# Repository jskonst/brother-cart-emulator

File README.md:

# Картридж узоров CK-35

Проект про картридж Brother CK-35: страница по Wi-Fi, на которой рисуют узор, и плата, которая отдаёт его машине как память картриджа. Байтовый формат узора ещё не подтверждён дампом. Пока его нет, прошивка образ картриджа не собирает.

CK-35 своих узоров в памяти машины не хранит. Узор приходит с картриджа, картридж заполняет PPD-35, и машина умеет записать свою память обратно в картридж. Вставка картриджа очищает память машины. Это описание из [заметки ETI Berlin](https://etiberlin.wordpress.com/2013/12/16/the-ck-35-what-i-have-learned-so-far/) и руководств Cartridge Utility, не из нашего дампа. Поэтому оригинальный картридж сначала читают отдельным дампером и только потом снова ставят в машину или в PPD. Батарею на плате измеряют до этого: севшие элементы на таких картах обычны, и тогда ОЗУ уже пустое.

## Что где лежит

| Путь | Что это |
| --- | --- |
| `knitting-cart/` | Чертежи Грегора Рипла, Stitch Pattern Cartridge II и эмулятор на ATmega165PA. Лицензия CERN OHL 1.2, не MIT. Атрибуция в `knitting-cart/NOTICE.md`. Прошивки там нет |
| `firmware/ck35-editor/` | ESP32, точка доступа и страница с сеткой. JSON в LittleFS. Шину картриджа не трогает |
| `hardware/dumper/` | Читатель на Arduino Mega 2560. Только чтение: контакт записи удержан железом, контакт батареи на 5 В не сажается |
| `docs/` | Разбор, что известно про CK-35, и план |
| `legacy/` | Старый программатор вышивальной карты. В CK-35 не вставлять |

Сборка редактора: `pio run` в `firmware/ck35-editor/`. Сборка дампера: `arduino-cli compile --fqbn arduino:avr:mega hardware/dumper/mega/ck35_dump`.

Редактор поднимает сеть `CK35-Editor`, пароль `ck35-editor`, адрес `http://192.168.4.1/`. Домашний Wi-Fi подхватывается только если в LittleFS лежит `/sta.txt` из двух строк. Пароль точки доступа напечатан в UART и его стоит сменить в `pattern_editor.cpp`.

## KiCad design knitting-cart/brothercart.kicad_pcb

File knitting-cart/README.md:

# Brother Pattern Programming Devices

Various electronic experiments with pattern programming on Brother knitting machines.

## brothercart

Reverse engineering of the Stitch Pattern Cartridge II.

This card is equipped with 32KB RAM and 32KB ROM.
The ROM is an EPROM without erase window and probably contains some built-in
knitting patterns. The RAM can be programmed freely.

To ensure data retention on the RAM chip, there is a huge 3V lithium battery
soldered onto the PCB. There is also some discrete logic to support memory
bank switching (probably).

## emulator

A re-implementation of the memory cartridge with a microcontroller, an SPI
flash chip (optional, 64KB..512KB), and a microSD card slot.

The cartridge memory bus is directly attached to the microcontroller.

Memory access will not be as fast as the original RAM and ROM, so make sure
not to run the bus faster than the microcontroller can feed data.

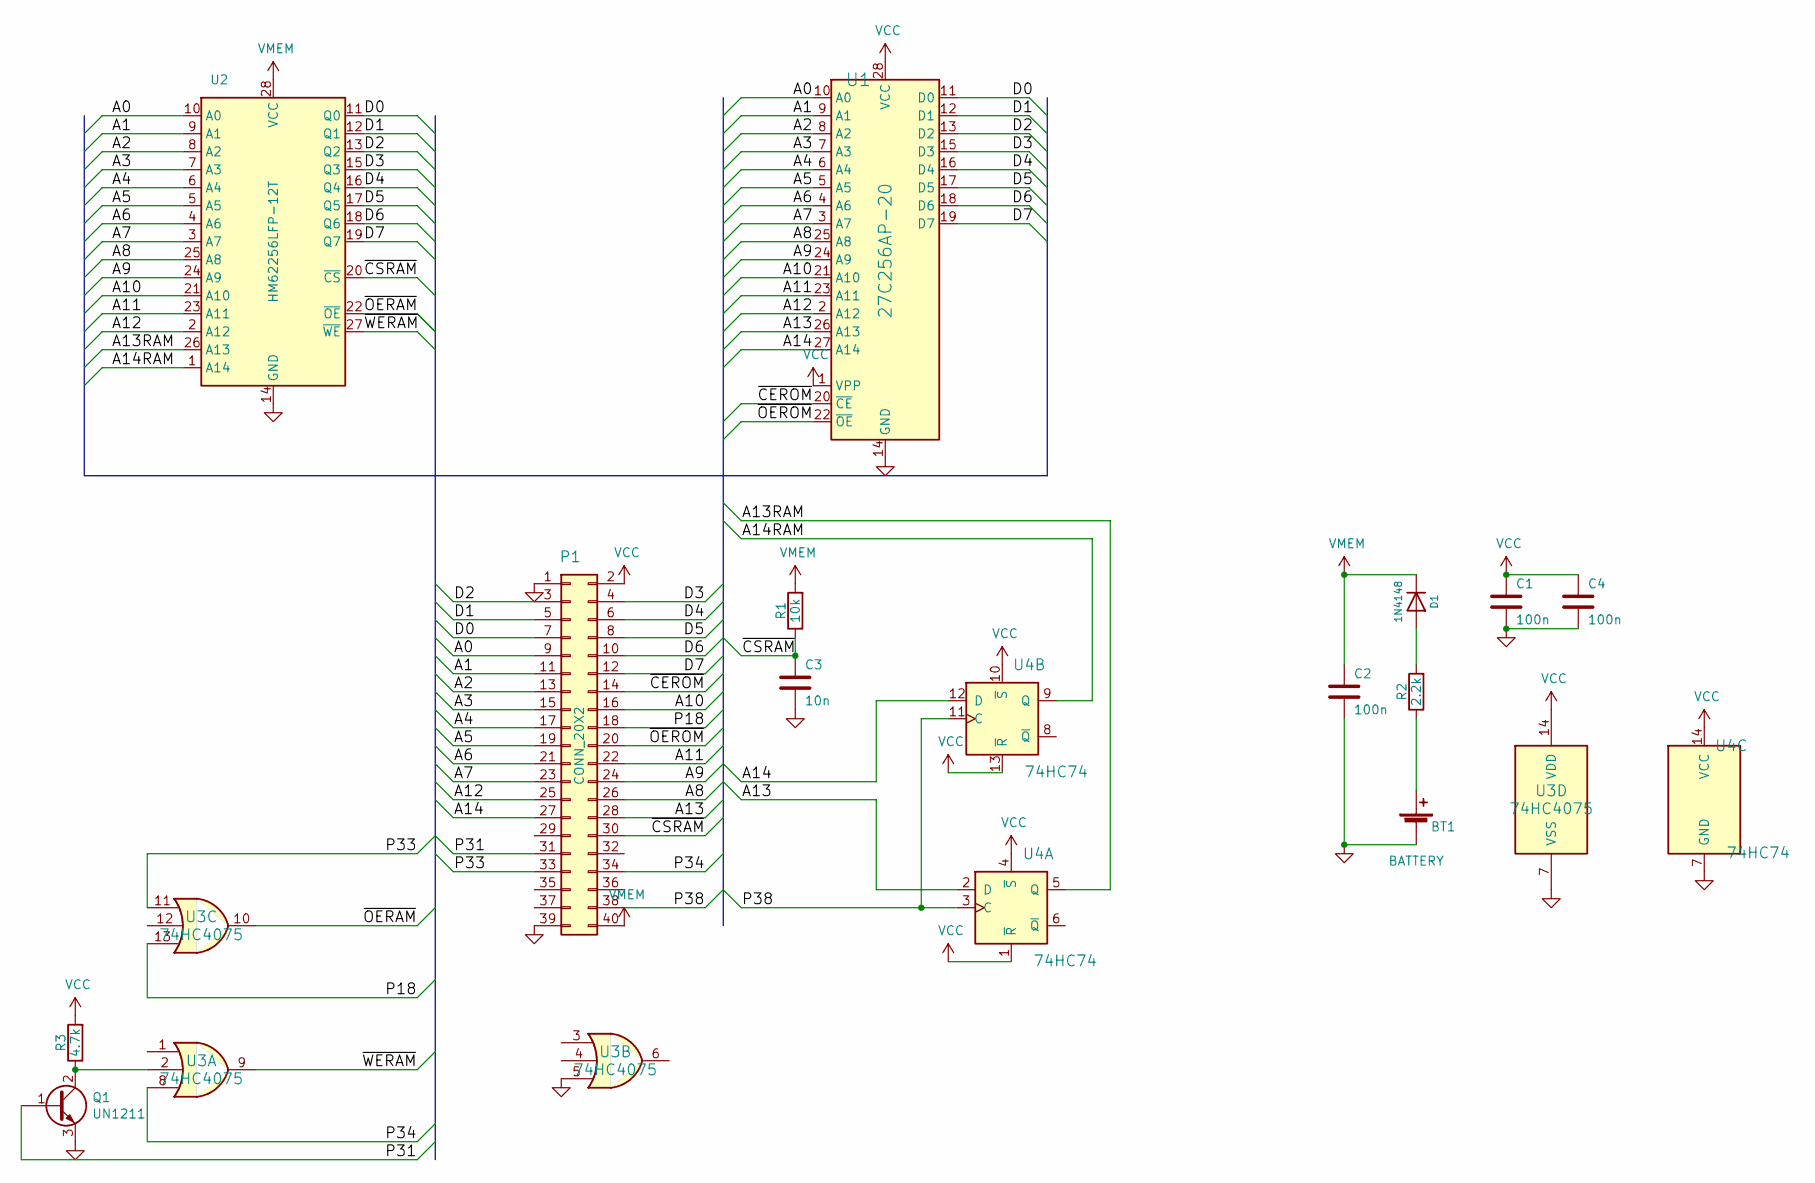
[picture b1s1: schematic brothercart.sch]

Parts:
BT1: BATTERY
C1, C2, C4: 100n; C_Disc_D6.0mm_W2.5mm_P5.00mm
C3: 10n; C_Disc_D4.3mm_W1.9mm_P5.00mm
D1: 1N4148; D_DO-15_P10.16mm_Horizontal
P1: CONN_20X2; Samtec_MECF-20-0_-NP-L-DV_2x20_P1.27mm_Edge
Q1: UN1211; TO-92L_Inline_Wide
R1: 10k; R_Axial_DIN0207_L6.3mm_D2.5mm_P10.16mm_Horizontal
R2: 2.2k; R_Axial_DIN0207_L6.3mm_D2.5mm_P10.16mm_Horizontal
R3: 4.7k; R_Axial_DIN0207_L6.3mm_D2.5mm_P10.16mm_Horizontal
U1: 27C256AP-20; SOIC-28W_7.5x17.9mm_P1.27mm
U2: HM62256LFP-12T; SOIC-28W_7.5x17.9mm_P1.27mm
U3: 74HC4075; SO-14_5.3x10.2mm_P1.27mm
U4: 74HC74; SO-14_5.3x10.2mm_P1.27mm

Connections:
/A0: P1.9, U1.10 (A0), U2.10 (A0)
/A1: P1.11, U1.9 (A1), U2.9 (A1)
/A2: P1.13, U1.8 (A2), U2.8 (A2)
/A3: P1.15, U1.7 (A3), U2.7 (A3)
/A4: P1.17, U1.6 (A4), U2.6 (A4)
/A5: P1.19, U1.5 (A5), U2.5 (A5)
/A6: P1.21, U1.4 (A6), U2.4 (A6)
/A7: P1.23, U1.3 (A7), U2.3 (A7)
/A8: P1.26, U1.25 (A8), U2.25 (A8)
/A9: P1.24, U1.24 (A9), U2.24 (A9)
/A10: P1.16, U1.21 (A10), U2.21 (A10)
/A11: P1.22, U1.23 (A11), U2.23 (A11)
/A12: P1.25, U1.2 (A12), U2.2 (A12)
/A13: P1.28, U1.26 (A13), U4.2 (D)
/A13RAM: U2.26 (A13), U4.5 (Q)
/A14: P1.27, U1.27 (A14), U4.12 (D)
/A14RAM: U2.1 (A14), U4.9 (Q)
/D0: P1.7, U1.11 (D0), U2.11 (Q0)
/D1: P1.5, U1.12 (D1), U2.12 (Q1)
/D2: P1.3, U1.13 (D2), U2.13 (Q2)
/D3: P1.4, U1.15 (D3), U2.15 (Q3)
/D4: P1.6, U1.16 (D4), U2.16 (Q4)
/D5: P1.8, U1.17 (D5), U2.17 (Q5)
/D6: P1.10, U1.18 (D6), U2.18 (Q6)
/D7: P1.12, U1.19 (D7), U2.19 (Q7)
/P18: P1.18, U3.13
/P31: P1.31, Q1.1 (B)
/P33: P1.33, U3.11
/P34: P1.34, U3.8
/P38: P1.38, U4.3 (C), U4.11 (C)
/~CEROM: P1.14, U1.20 (~CE)
/~CSRAM: C3.1, P1.30, R1.1, U2.20 (~CS)
/~OERAM: U2.22 (~OE), U3.10
/~OEROM: P1.20, U1.22 (~OE)
/~WERAM: U2.27 (~WE), U3.9
GND: BT1.2 (-), C1.2, C2.2, C3.2, C4.2, P1.1, P1.39, Q1.3 (E), U1.14 (GND), U2.14 (GND), U3.5, U3.7 (VSS), U4.7 (GND)
unnamed: BT1.1 (+), R2.1
unnamed: D1.2 (A), R2.2
unnamed: Q1.2 (C), R3.1, U3.2
VCC: C1.1, C4.1, P1.2, R3.2, U1.1 (VPP), U1.28 (VCC), U3.14 (VDD), U4.1 (~R), U4.4 (~S), U4.10 (~S), U4.13 (~R), U4.14 (VCC)
VMEM: C2.1, D1.1 (K), P1.40, R1.2, U2.28 (VCC)

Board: 2 copper layers, 14 parts (1 on the bottom side), 40 nets, no tracks yet.

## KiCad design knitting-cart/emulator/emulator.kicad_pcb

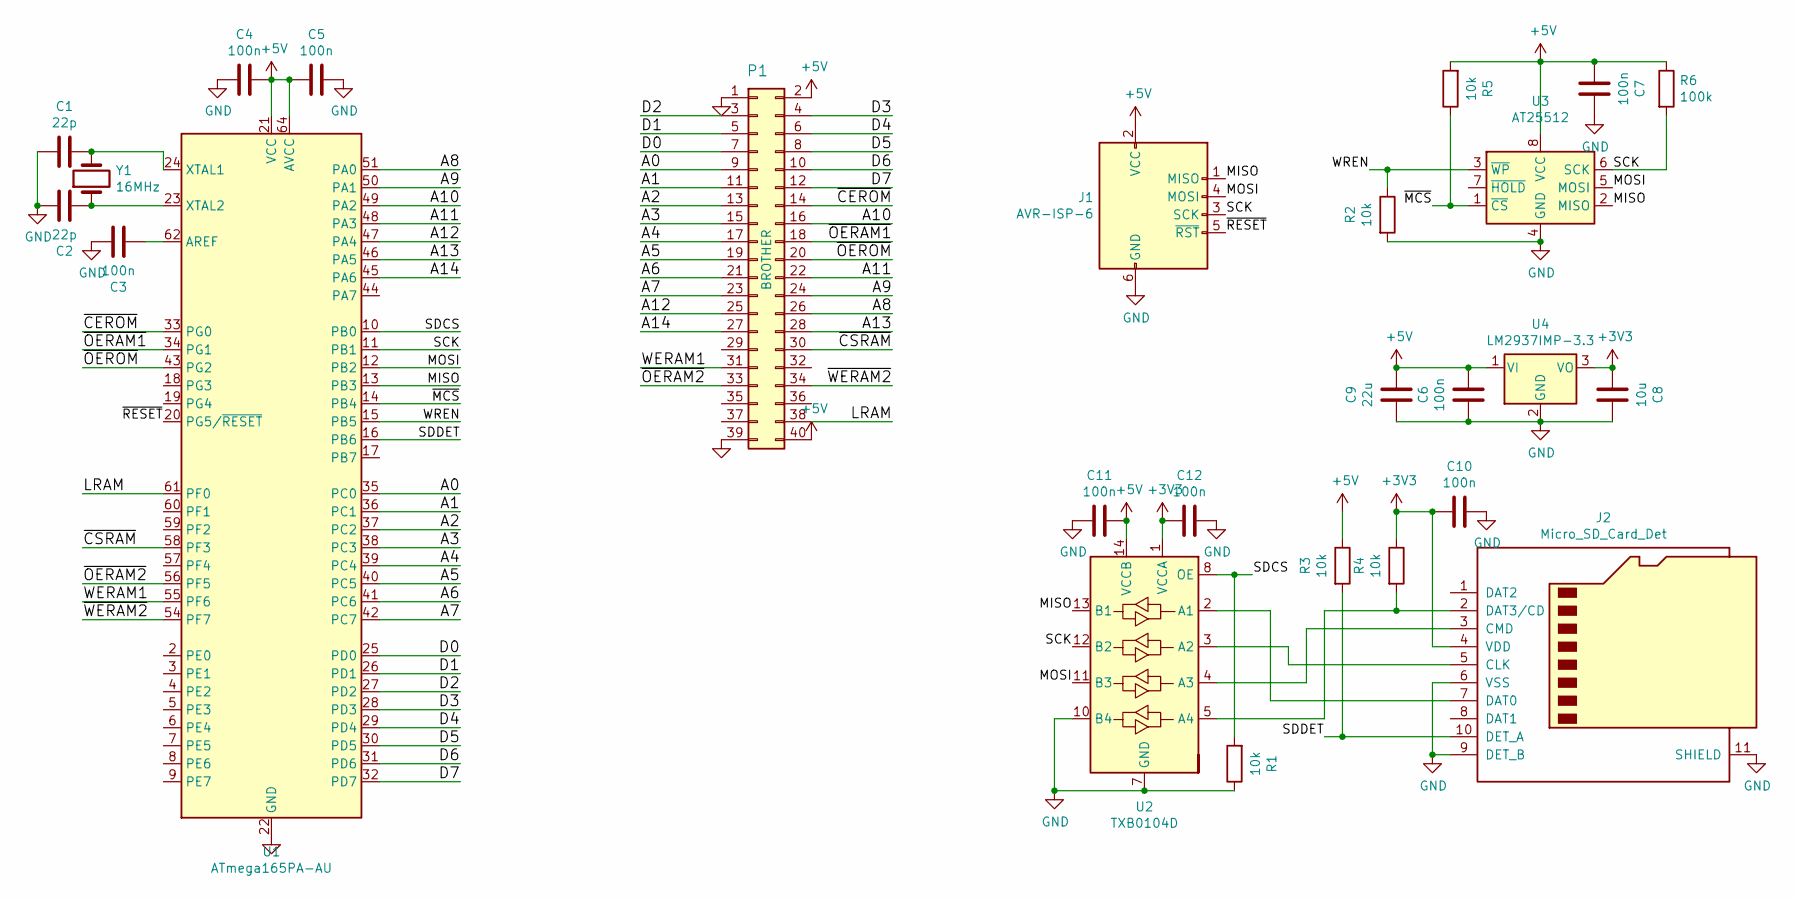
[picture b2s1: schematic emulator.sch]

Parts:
C1, C2: 22p; C_0805_2012Metric
C3, C4, C5, C6, C7, C10, C11, C12: 100n; C_0805_2012Metric
C8: 10u; C_0805_2012Metric
C9: 22u; C_0805_2012Metric
J1: AVR-ISP-6; PinHeader_2x03_P2.54mm_Horizontal
J2: Micro_SD_Card_Det; microSD_HC_Hirose_DM3D-SF
P1: BROTHER; Brother_Pattern_Cartridge_2x20_P1.27_W26.2
R1, R2, R3, R4, R5: 10k; R_0805_2012Metric_Pad1.20x1.40mm_HandSolder
R6: 100k; R_0805_2012Metric
U1: ATmega165PA-AU; TQFP-64_14x14mm_P0.8mm
U2: TXB0104D; SOIC-14_3.9x8.7mm_P1.27mm
U3: AT25512; SOIC-8_3.9x4.9mm_P1.27mm
U4: LM2937IMP-3.3; SOT-223-3_TabPin2
Y1: 16MHz; Crystal_SMD_HC49-SD

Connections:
+3V3: C8.2, C10.2, C12.2, J2.4 (VDD), R4.1, U2.1 (VCCA), U4.3 (VO)
+5V: C4.1, C5.2, C6.1, C7.2, C9.1, C11.1, J1.2 (VCC), P1.2, P1.40, R3.1, R5.2, R6.1, U1.21 (VCC), U1.52 (VCC), U1.64 (AVCC), U2.14 (VCCB), U3.8 (VCC), U4.1 (VI)
/A0: P1.9, U1.35 (PC0)
/A1: P1.11, U1.36 (PC1)
/A2: P1.13, U1.37 (PC2)
/A3: P1.15, U1.38 (PC3)
/A4: P1.17, U1.39 (PC4)
/A5: P1.19, U1.40 (PC5)
/A6: P1.21, U1.41 (PC6)
/A7: P1.23, U1.42 (PC7)
/A8: P1.26, U1.51 (PA0)
/A9: P1.24, U1.50 (PA1)
/A10: P1.16, U1.49 (PA2)
/A11: P1.22, U1.48 (PA3)
/A12: P1.25, U1.47 (PA4)
/A13: P1.28, U1.46 (PA5)
/A14: P1.27, U1.45 (PA6)
/D0: P1.7, U1.25 (PD0)
/D1: P1.5, U1.26 (PD1)
/D2: P1.3, U1.27 (PD2)
/D3: P1.4, U1.28 (PD3)
/D4: P1.6, U1.29 (PD4)
/D5: P1.8, U1.30 (PD5)
/D6: P1.10, U1.31 (PD6)
/D7: P1.12, U1.32 (PD7)
/LRAM: P1.38, U1.61 (PF0)
/MISO: J1.1 (MISO), U1.13 (PB3), U2.13 (B1), U3.2 (MISO)
/MOSI: J1.4 (MOSI), U1.12 (PB2), U2.11 (B3), U3.5 (MOSI)
/SCK: J1.3 (SCK), R6.2, U1.11 (PB1), U2.12 (B2), U3.6 (SCK)
/SDCS: R1.2, U1.10 (PB0), U2.8 (OE)
/SDDET: J2.10 (DET_A), R3.2, U1.16 (PB6)
/WERAM1: P1.31, U1.55 (PF6)
/WREN: R2.1, U1.15 (PB5), U3.3 (~WP)
/~CEROM: P1.14, U1.33 (PG0)
/~CSRAM: P1.30, U1.58 (PF3)
/~MCS: R5.1, U1.14 (PB4), U3.1 (~CS)
/~OERAM1: P1.18, U1.34 (PG1)
/~OERAM2: P1.33, U1.56 (PF5)
/~OEROM: P1.20, U1.43 (PG2)
/~RESET: J1.5 (~RST), U1.20 (PG5/~RESET)
/~WERAM2: P1.34, U1.54 (PF7)
GND: C1.2, C2.1, C3.1, C4.2, C5.1, C6.2, C7.1, C8.1, C9.2, C10.1, C11.2, C12.1, J1.6 (GND), J2.6 (VSS), J2.9 (DET_B), J2.11 (SHIELD), P1.1, P1.39, R1.1, R2.2, U1.22 (GND), U1.53 (GND), U1.63 (GND), U2.7 (GND), U2.10 (B4), U3.4 (GND), U4.2 (GND)
unnamed: C1.1, U1.24 (XTAL1), Y1.2
unnamed: C2.2, U1.23 (XTAL2), Y1.1
unnamed: C3.2, U1.62 (AREF)
unnamed: J2.2 (DAT3/CD), R4.2, U2.5 (A4)
unnamed: J2.3 (CMD), U2.4 (A3)
unnamed: J2.5 (CLK), U2.3 (A2)
unnamed: J2.7 (DAT0), U2.2 (A1)

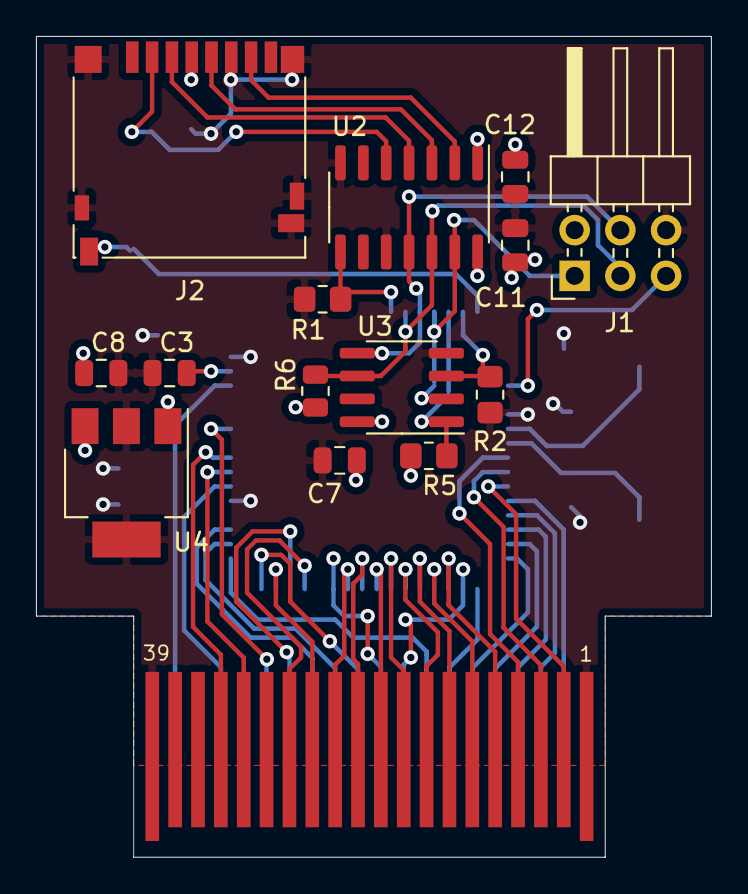
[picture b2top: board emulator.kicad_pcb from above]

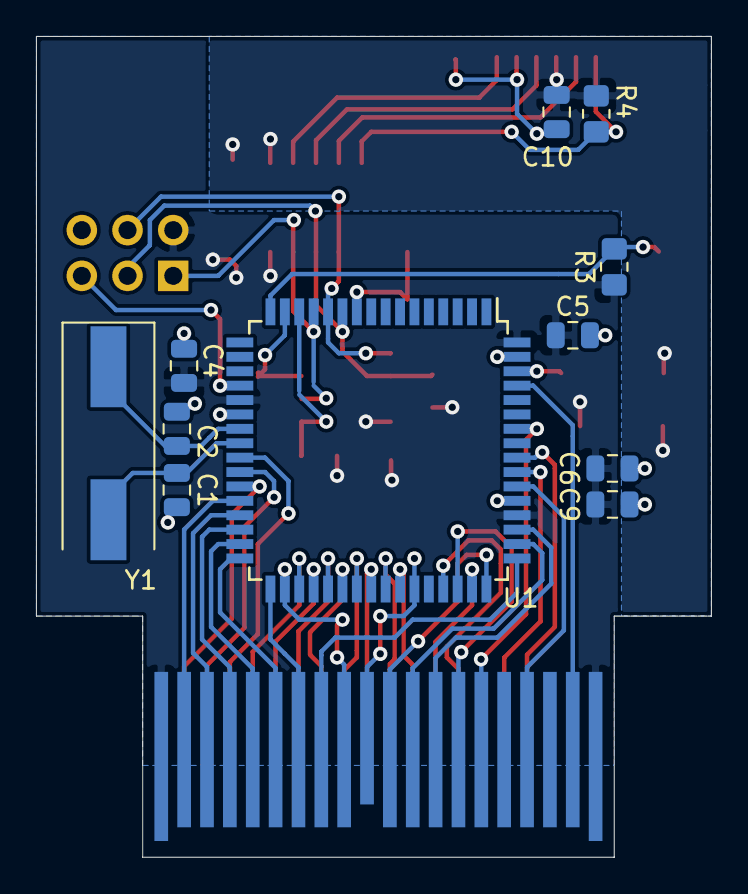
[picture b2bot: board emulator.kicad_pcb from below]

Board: 2 copper layers, 37.5 x 45.6 mm, 26 parts (11 on the bottom side), 49 nets.

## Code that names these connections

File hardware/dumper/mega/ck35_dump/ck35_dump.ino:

// CK-35 / Stitch Pattern Cartridge read-only dumper.
// MIT for this sketch. Pin names come from seto/brother (CERN OHL 1.2):
// knitting-cart/brothercart.sch and the emulator rename in emulator/emulator.sch.
//
// This sketch never drives a write. Pin 31 (P31 / WERAM1) is not a GPIO:
// the board ties it to GND. Pin 34 (P34 / ~WERAM2) is held HIGH.
// Pin 40 (VMEM) is only measured through a divider. It is not powered.

static const uint8_t ADDR[15] = {
    22, 23, 24, 25, 26, 27, 28, 29, 30, 31, 32, 33, 34, 35, 36};
static const uint8_t DATA[8] = {37, 38, 39, 40, 41, 42, 43, 44};

static const uint8_t PIN_CEROM = 46;  // active low, edge pin 14
static const uint8_t PIN_OEROM = 47;  // active low, edge pin 20
static const uint8_t PIN_CSRAM = 48;  // active low, edge pin 30
static const uint8_t PIN_P18 = 49;    // emulator name ~OERAM1, edge pin 18
static const uint8_t PIN_P33 = 50;    // emulator name ~OERAM2, edge pin 33
static const uint8_t PIN_P34 = 51;    // emulator name ~WERAM2, edge pin 34, always HIGH
static const uint8_t PIN_P38 = 52;    // emulator name LRAM, edge pin 38, 74HC74 clock
static const uint8_t PIN_VMEM = A0;   // edge pin 40, sense only

static const uint16_t DUMP_LEN = 32768;

static void setAddr(uint16_t addr) {
  for (uint8_t i = 0; i < 15; i++) {
    digitalWrite(ADDR[i], (addr >> i) & 1);
  }
}

static uint8_t readData() {
  uint8_t value = 0;
  for (uint8_t i = 0; i < 8; i++) {
    if (digitalRead(DATA[i])) value |= (1 << i);
  }
  return value;
}

static void idleStrobes() {
  digitalWrite(PIN_CEROM, HIGH);
  digitalWrite(PIN_OEROM, HIGH);
  digitalWrite(PIN_CSRAM, HIGH);
  digitalWrite(PIN_P18, HIGH);
  digitalWrite(PIN_P33, HIGH);
  digitalWrite(PIN_P34, HIGH);
  digitalWrite(PIN_P38, LOW);
}

static void pulseLatch() {
  // brothercart.sch: 74HC74 clocks A13/A14 into A13RAM/A14RAM on rising P38.
  // That selects a RAM address. It is not a write while ~WERAM stays high.
  digitalWrite(PIN_P38, LOW);
  delayMicroseconds(2);
  digitalWrite(PIN_P38, HIGH);
  delayMicroseconds(2);
  digitalWrite(PIN_P38, LOW);
}

static uint8_t readRomByte(uint16_t addr) {
  setAddr(addr);
  digitalWrite(PIN_CSRAM, HIGH);
  digitalWrite(PIN_P18, HIGH);
  digitalWrite(PIN_P33, HIGH);
  digitalWrite(PIN_P34, HIGH);
  digitalWrite(PIN_P38, LOW);
  digitalWrite(PIN_CEROM, LOW);
  digitalWrite(PIN_OEROM, LOW);
  delayMicroseconds(5);
  uint8_t value = readData();
  digitalWrite(PIN_CEROM, HIGH);
  digitalWrite(PIN_OEROM, HIGH);
  return value;
}

static uint8_t readRamByte(uint16_t addr) {
  setAddr(addr);
  pulseLatch();
  digitalWrite(PIN_CEROM, HIGH);
  digitalWrite(PIN_OEROM, HIGH);
  // Hypothesis from brothercart.sch, not confirmed on B442076-1:
  // ~OERAM = P18 OR P33 OR an unwired gate input. Both low lets the RAM drive.
  digitalWrite(PIN_P18, LOW);
  digitalWrite(PIN_P33, LOW);
  digitalWrite(PIN_P34, HIGH);
  digitalWrite(PIN_CSRAM, LOW);
  delayMicroseconds(5);
  uint8_t value = readData();
  digitalWrite(PIN_CSRAM, HIGH);
  digitalWrite(PIN_P18, HIGH);
  digitalWrite(PIN_P33, HIGH);
  return value;
}

static void dumpRegion(const char* name, uint8_t (*reader)(uint16_t)) {
  Serial.print("BEGIN ");
  Serial.print(name);
  Serial.print(" ");
  Serial.println(DUMP_LEN);
  Serial.flush();
  for (uint32_t addr = 0; addr < DUMP_LEN; addr++) {
    Serial.write(reader((uint16_t)addr));
  }
  Serial.flush();
  Serial.print("END ");
  Serial.println(name);
  Serial.flush();
}

static float readVmem() {
  // 100k / 100k divider. 5 V at the pin reads about 2.5 V on A0.
  long sum = 0;
  for (uint8_t i = 0; i < 8; i++) sum += analogRead(PIN_VMEM);
  float volts = (sum / 8.0f) * (5.0f / 1023.0f) * 2.0f;
  return volts;
}

void setup() {
  for (uint8_t i = 0; i < 15; i++) {
    pinMode(ADDR[i], OUTPUT);
    digitalWrite(ADDR[i], LOW);
  }
  for (uint8_t i = 0; i < 8; i++) pinMode(DATA[i], INPUT);
  pinMode(PIN_CEROM, OUTPUT);
  pinMode(PIN_OEROM, OUTPUT);
  pinMode(PIN_CSRAM, OUTPUT);
  pinMode(PIN_P18, OUTPUT);
  pinMode(PIN_P33, OUTPUT);
  pinMode(PIN_P34, OUTPUT);
  pinMode(PIN_P38, OUTPUT);
  idleStrobes();

  Serial.begin(115200);
  analogReference(DEFAULT);
  delay(200);
  idleStrobes();

  Serial.println("CK35-DUMP 1");
  Serial.println("READ ONLY. Pin 31 tied to GND. Pin 34 held high. Pin 40 is sense only.");
  float vmem = readVmem();
  Serial.print("VMEM_EST_V ");
  Serial.println(vmem, 2);
  if (vmem < 2.0f) {
    Serial.println("WARN battery looks low or pin 40 is open. RAM may already be empty. Do not replace the cell to chase a dump.");
  }
  Serial.println("Send G to dump. Dump the cartridge before it goes back into a CK-35 or a PPD.");
}

void loop() {
  if (Serial.available() && Serial.read() == 'G') {
    while (Serial.available()) Serial.read();
    idleStrobes();
    dumpRegion("ROM", readRomByte);
    dumpRegion("RAM", readRamByte);
    idleStrobes();
    Serial.println("DONE");
  }
}
